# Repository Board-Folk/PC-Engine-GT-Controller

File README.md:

# PC-Engine-GT-Controller
This repository contains a recreation and a remaster of the
controller board PCB for PC Engine GT Handheld.

## Original Controller PCB

The original recreation is based on the reverse engineering of the original
PCB and schematics using scanned images of the original
board's copper layers, so should be a reasonably accurate reproduction.

## Remaster Controller PCB

The remaster is based on the schematics of the pc engine console controller which
uses logic chips to control the user input into the GT Handheld.
Some functionality is lost using this board, such as using the Link Cable and
no sleep functionality for the screen.

## PCB Production

Minimum track widths, clearances and via sizes are within the standard
offering of modern PCB fabricators. Development was done using JLCPCB and as
such the Gerber files are provided to their specification.

The design is verified to work as a 2-layer PCB.

## Bill of Materials

Most parts are marked on the board and it is expected that these will be reused
from a donor board. It is completely possible that your particular board uses
different (but compatible) parts so it's advisable to take photos before starting.

[**Interactive BOM Original**][IBOM-Original]

[**Interactive BOM Remaster**][IBOM-Remaster]

## Thanks

  * Rob Taylor ([@PeepoUK](https://github.com/PeepoUK)) for doing most of
    the PCB layout.\
&nbsp;
  * Simon "Aergan" Lock ([@Aergan](https://github.com/Aergan)),\
    Cosam (@cosam_the_great),\
    Dennis (@PointerFunction),\
    Leo Oliveria (@leo__oliveira),\
    Zaxour 阿宅, (@zaxour),\
    Ian Cudlip (@grandoldian)\
    for their insights, support and testing of the prototype boards.\
&nbsp;
  * The rest of the Board Folk Team for their support and general
    coolness.\
&nbsp;

## Legal

As the product of this project is a replica of a proprietary product, the
the author makes no claim of copyright to the schematics nor PCB layouts and
releases these into the public domain, solely for the purposes of study and
historical preservation.

You are free to produce PCBs based on this project's designs at your own risk
and without limitation, for your own use or for sale and/or repair at a
reasonable price. Attribution is appreciated. The authors are not obliged to
provide support of any kind.

Under no circumstances will the authors be held responsible or liable in any
way for losses, damages or costs resulting from the use of the information
and/or resources of this project.

The resources are provided "as-is" without warranty of any kind, either
expressed or implied, including, but not limited to, the implied warranties
of merchantability and fitness for a particular purpose.

[IBOM-Original]: http://htmlpreview.github.io/?https://raw.githubusercontent.com/Board-Folk/PC-Engine-GT-Controller/main/original-7610-0641-A/bom/PC%20Engine%20GT%20Controller%20PCB.html

[IBOM-Remaster]: http://htmlpreview.github.io/?https://raw.githubusercontent.com/Board-Folk/PC-Engine-GT-Controller/main/remaster/bom/PC%20Engine%20GT%20Controller%20BOM.html

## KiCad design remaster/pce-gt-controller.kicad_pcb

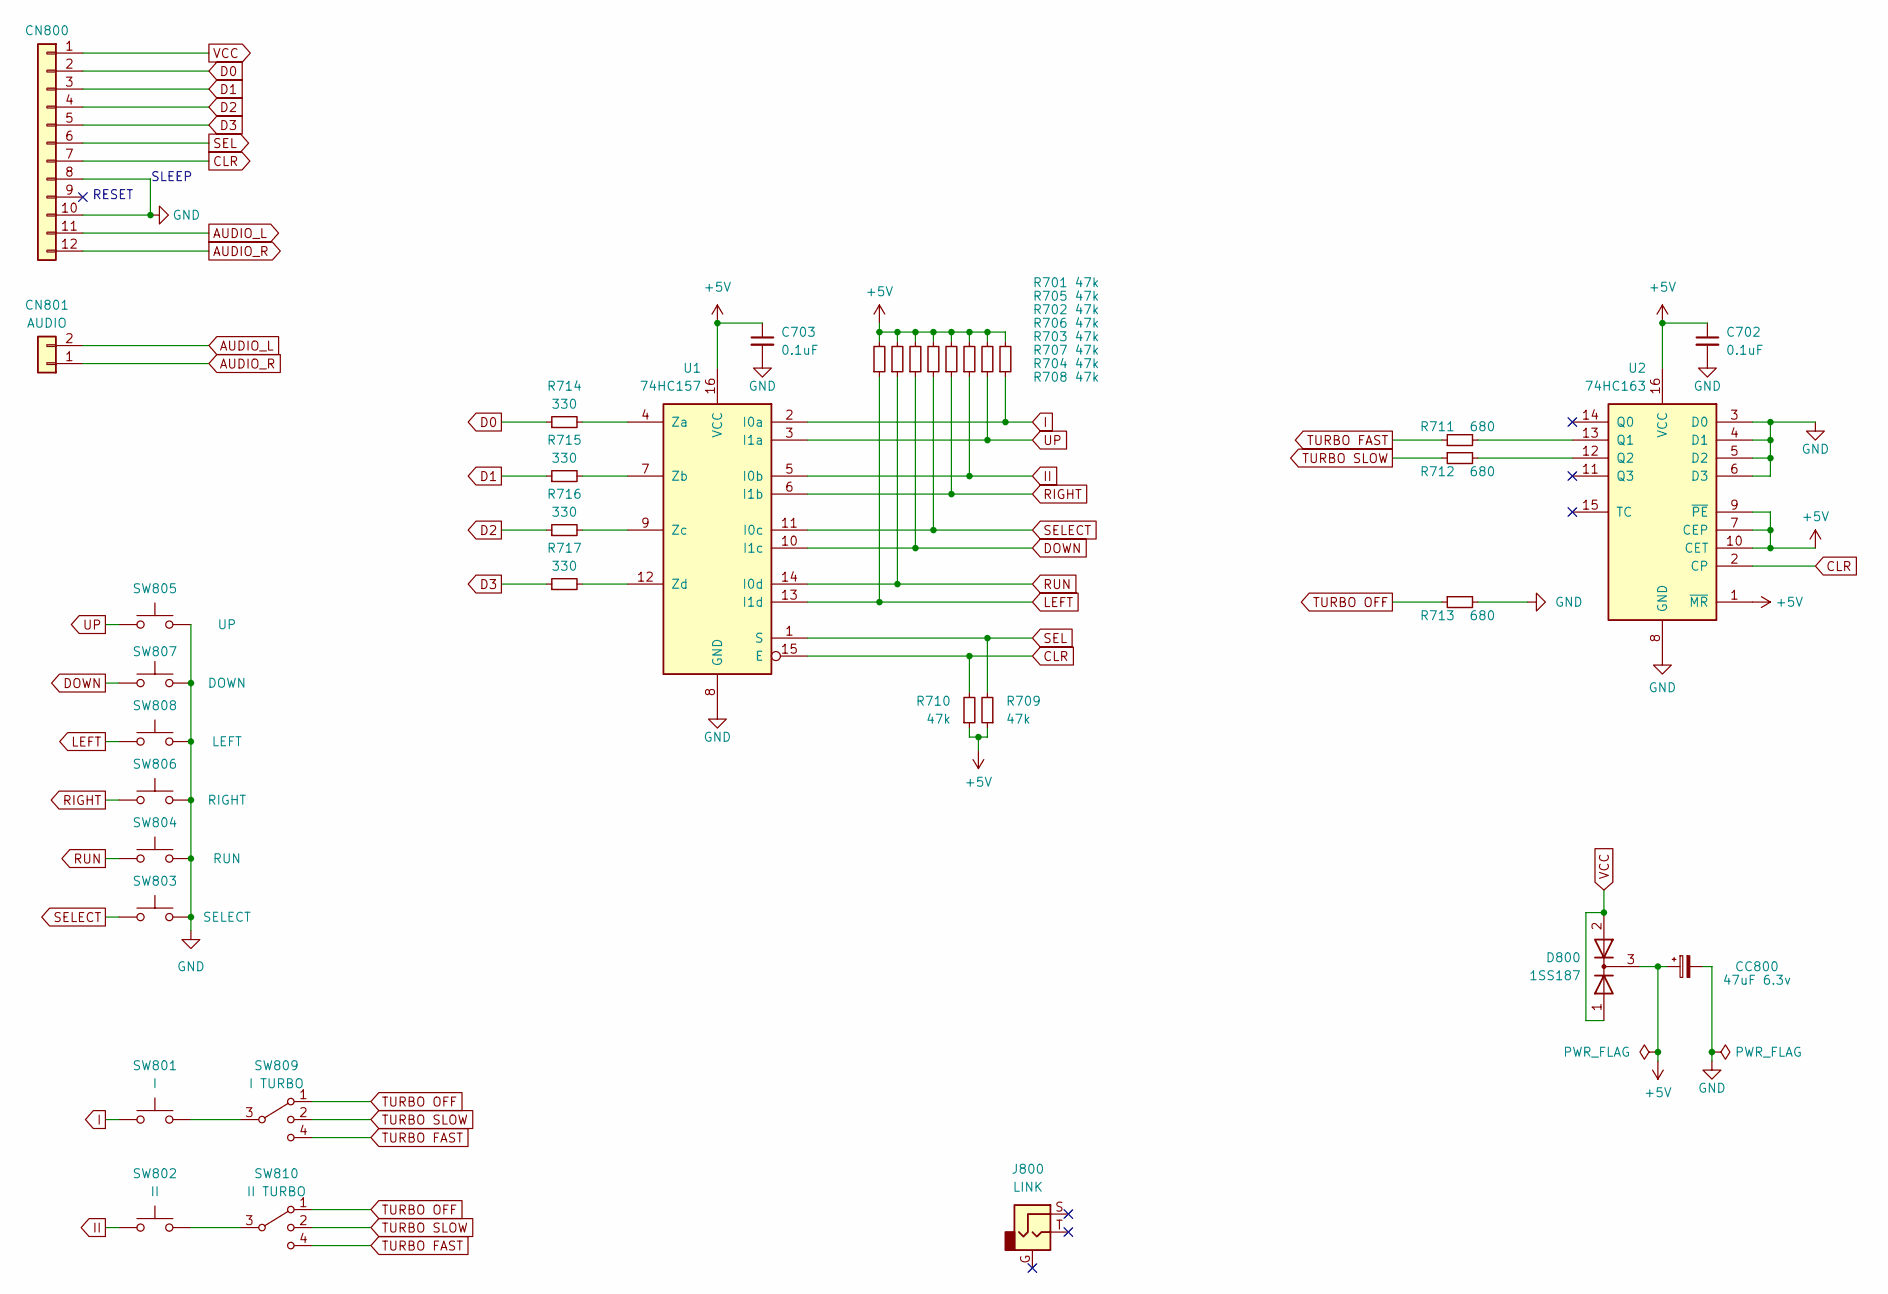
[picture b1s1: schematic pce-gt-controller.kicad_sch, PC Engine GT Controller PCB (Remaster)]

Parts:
C702, C703: 0.1uF; R_0805_2012Metric
CC800: 47uF 6.3v; CP_Radial_D5.0mm_P2.50mm
CN800: Conn_01x12; CN800
CN801: AUDIO; CN801
D800: 1SS187; Diode SOT-23
J800: LINK; J800
R701, R702, R703, R704, R705, R706, R707, R708, R709, R710: 47k; R_0805_2012Metric
R711, R712, R713: 680; R_0805_2012Metric
R714, R715, R716, R717: 330; R_0805_2012Metric
SW801: I; Switch Type 3
SW802: II; Switch Type 2
SW803: SELECT; Switch Type 1
SW804: RUN; Switch Type 1
SW805: UP; Switch Type 4
SW806: RIGHT; Switch Type 5
SW807: DOWN; Switch Type 4
SW808: LEFT; Switch Type 5
SW809: I TURBO; Turbo Switch
SW810: II TURBO; Turbo Switch
U1: 74HC157; SOIC-16_3.9x9.9mm_P1.27mm
U2: 74HC163; SOIC-16_3.9x9.9mm_P1.27mm

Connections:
+5V: C702.1, C703.1, CC800.1, D800.3 (K), R701.2, R702.2, R703.2, R704.2, R705.2, R706.2, R707.2, R708.2, R709.1, R710.1, U1.16 (VCC), U2.1 (~MR), U2.7 (CEP), U2.9 (~PE), U2.10 (CET), U2.16 (VCC)
AUDIO_L: CN800.11, CN801.2
AUDIO_R: CN800.12, CN801.1
CLR: CN800.7, R710.2, U1.15 (E), U2.2 (CP)
D0: CN800.2, R714.1
D1: CN800.3, R715.1
D2: CN800.4, R716.1
D3: CN800.5, R717.1
DOWN: R707.1, SW807.1, U1.10 (I1c)
GND: C702.2, C703.2, CC800.2, CN800.8, CN800.10, R713.2, SW803.2, SW804.2, SW805.2, SW806.2, SW807.2, SW808.2, U1.8 (GND), U2.3 (D0), U2.4 (D1), U2.5 (D2), U2.6 (D3), U2.8 (GND)
I: R701.1, SW801.1, U1.2 (I0a)
II: R702.1, SW802.1, U1.5 (I0b)
LEFT: R708.1, SW808.1, U1.13 (I1d)
unnamed: SW801.2, SW809.3
unnamed: SW802.2, SW810.3
unnamed: R714.2, U1.4 (Za)
unnamed: R715.2, U1.7 (Zb)
unnamed: R716.2, U1.9 (Zc)
unnamed: R717.2, U1.12 (Zd)
unnamed: R711.2, U2.13 (Q1)
unnamed: R712.2, U2.12 (Q2)
RIGHT: R706.1, SW806.1, U1.6 (I1b)
RUN: R704.1, SW804.1, U1.14 (I0d)
SEL: CN800.6, R709.2, U1.1 (S)
SELECT: R703.1, SW803.1, U1.11 (I0c)
TURBO FAST: R711.1, SW809.4, SW810.4
TURBO OFF: R713.1, SW809.1, SW810.1
TURBO SLOW: R712.1, SW809.2, SW810.2
UP: R705.1, SW805.1, U1.3 (I1a)
VCC: CN800.1, D800.1 (A), D800.2 (A)

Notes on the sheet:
RESET
SLEEP

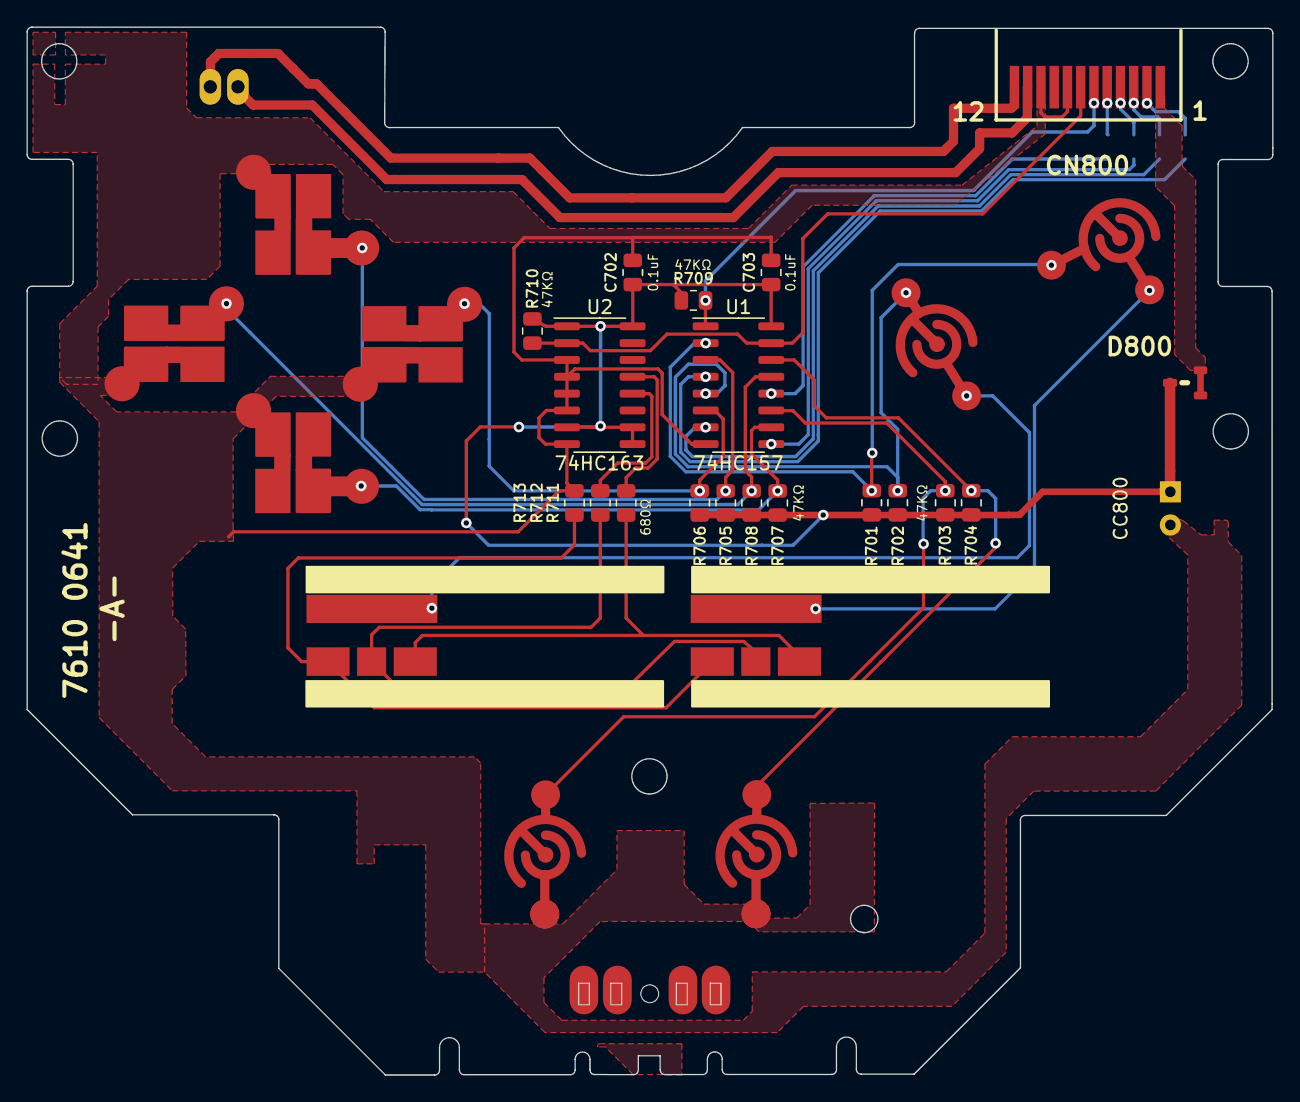
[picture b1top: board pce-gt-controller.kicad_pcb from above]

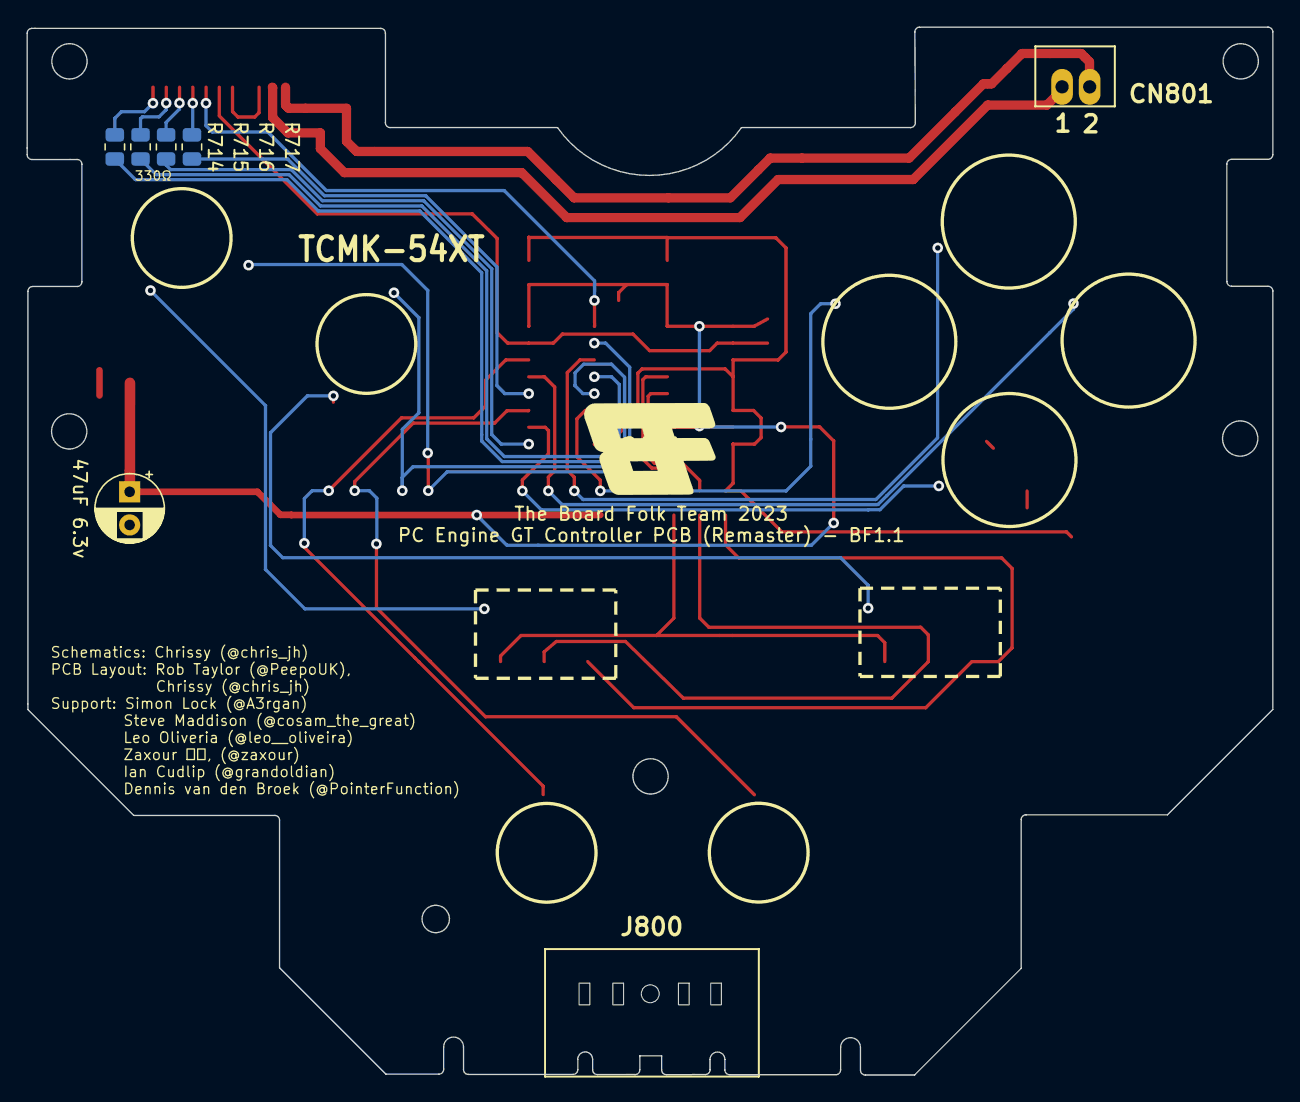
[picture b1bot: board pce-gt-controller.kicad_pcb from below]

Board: 2 copper layers, 94.0 x 79.1 mm, 36 parts (5 on the bottom side), 30 nets.

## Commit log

2023-11-06 Schematics for PCEGT-Controller
2023-11-06 Adding gitignore for backups
2023-11-07 Fix Link
2023-11-08 Updates
    Complete?
2023-11-08 Added TCMK silkscreen
2023-11-08 Generated gerbers
2023-11-19 Moved into own folder
2023-12-31 Update to original, fix slight mistake linking fast turbo
2023-12-31 Added BoardFolk Silk, Tidy up
2023-12-31 Some Images
2023-12-31 more images
2024-01-01 Tweak to the images
